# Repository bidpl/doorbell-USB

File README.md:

# Wake On Doorbell (WoD) USB Dongle

A USB stick that sends a spacebar press when the doorbell is pressed. Used to wake a door surveillence monitor when someone rings the doorbell.

Takes a AC signal through the barrel jack (doorbell wires). The onboard microcontroller acts as a USB keyboard while monitoring the signal for a drop in the average voltage (doorbell pressed). When it detects the decrease in voltage, it sends a spacebar keypress to wake the computer.

Assembled WoD USB Dongle:

WoD USB Dongle installed on a PC

## The stick itself

v1.0
Yay it works!
No errors found during testing and use.

## Case

A press fit case for the PCB. It has some screw holes, but the press fit is enough to hold it in. The tab for the USB connector is sized to increase the thickness of the connector to ~2.2mm.

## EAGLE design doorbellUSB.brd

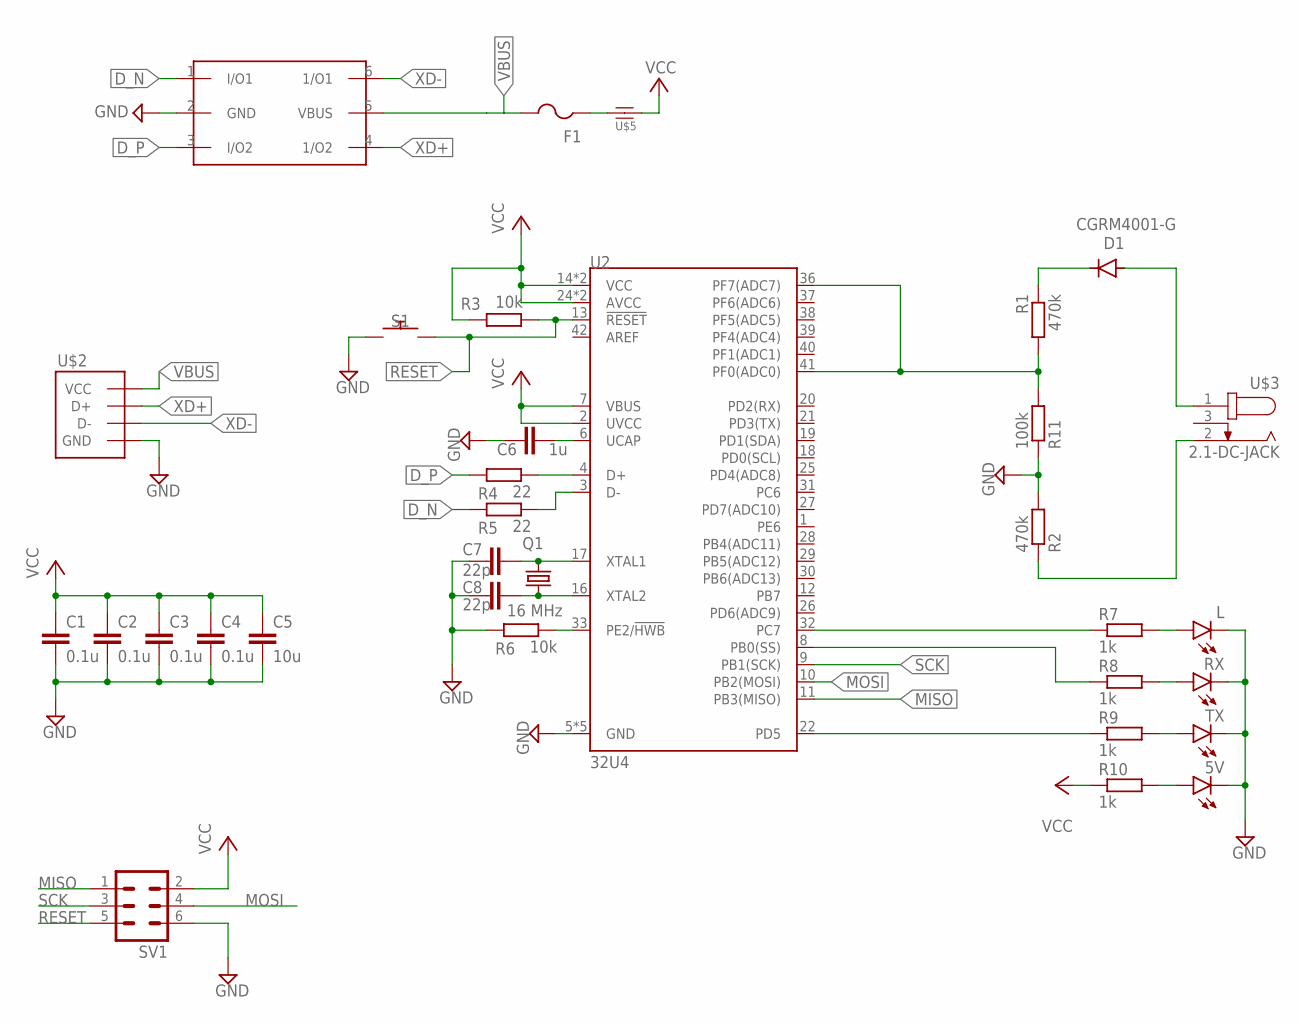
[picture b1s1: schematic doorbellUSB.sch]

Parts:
5V: LEDCHIP-LED0805; CHIP-LED0805
C1, C2, C3, C4: 0.1u; C0805
C5: 10u; C0805
C6: 1u; C0805
C7, C8: 22p; C0805
D1: CGRM4001-G; SOD-123_MINI-SMA
F1: PTCFUSE-1812; 1812
L: LEDCHIP-LED0805; CHIP-LED0805
Q1: 16 MHz; 5.0X3.2_2
R1, R2: 470k; R0805
R3, R6: 10k; R0805
R4, R5: 22; R0805
R7, R8, R9, R10: 1k; R0805
R11: 100k; R0805
RX: LEDCHIP-LED0805; CHIP-LED0805
S1: 3X4MM-PUHSBUTTON; 3X4MM-PUSHBUTTON
SV1: MA03-2
TX: LEDCHIP-LED0805; CHIP-LED0805
U2: 32U4; TQFP44
U$1: USBLC-2; SOT23-6L
U$2: PCB-USB-A; USB-A-ONBOARD
U$3: 2.1-DC-JACK; 2.1X5.5MM_JACK
U$5: FERRITE-BEAD; R0805

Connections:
DATA_N: R5.2, U2.3 (D-)
DATA_P: R4.2, U2.4 (D+)
D_N: R5.1, U$1.1 (I/O1)
D_P: R4.1, U$1.3 (I/O2)
GND: 5V.C, C1.2, C2.2, C3.2, C4.2, C5.2, C6.1, C7.2, C8.2, L.C, R2.2, R6.1, R11.1, RX.C, S1.P$1, SV1.6, TX.C, U2.5 (GND), U2.15 (GND), U2.23 (GND), U2.35 (GND), U2.43 (GND), U$1.2 (GND), U$2.GND
MISO: SV1.1, U2.11 (PB3(MISO))
MOSI: SV1.4, U2.10 (PB2(MOSI))
unnamed: R2.1, U$3.2
unnamed: D1.A, U$3.1
unnamed: D1.C, R1.1
unnamed: R1.2, R11.2, U2.36 (PF7(ADC7)), U2.41 (PF0(ADC0))
unnamed: R8.1, U2.8 (PB0(SS))
unnamed: C6.2, U2.6 (UCAP)
unnamed: R9.1, U2.22 (PD5)
unnamed: R7.1, U2.32 (PC7)
unnamed: L.A, R7.2
unnamed: R9.2, TX.A
unnamed: R6.2, U2.33 (PE2/!HWB)
unnamed: F1.1, U$5.2
unnamed: R8.2, RX.A
unnamed: 5V.A, R10.2
RESET: R3.2, S1.P$2, SV1.5, U2.13 (!RESET)
SCK: SV1.3, U2.9 (PB1(SCK))
VBUS: F1.2, U$1.5 (VBUS), U$2.VCC
VCC: C1.1, C2.1, C3.1, C4.1, C5.1, R3.1, R10.1, SV1.2, U2.2 (UVCC), U2.7 (VBUS), U2.14 (VCC), U2.24 (AVCC), U2.34 (VCC), U2.44 (AVCC), U$5.1
XD+: U$1.4 (1/O2), U$2.D+
XD-: U$1.6 (1/O1), U$2.D-
XTAL_1: C8.1, Q1.1, U2.16 (XTAL2)
XTAL_2: C7.1, Q1.2, U2.17 (XTAL1)

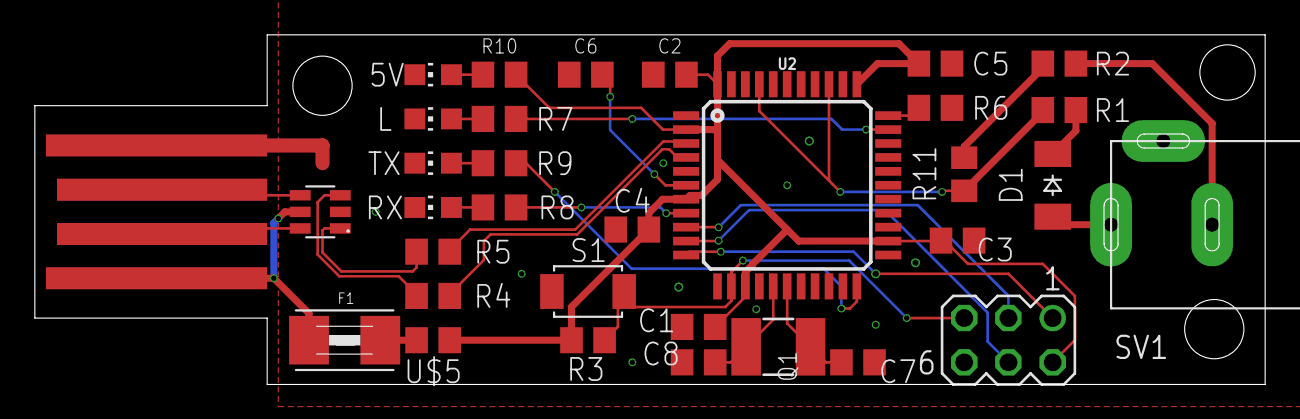
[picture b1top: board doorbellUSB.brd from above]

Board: 2 copper layers, 70.6 x 20.1 mm, 33 parts (0 on the bottom side), 29 nets.

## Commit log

2022-01-24 Turned project into git repo. Added images and README.md
2022-01-24 Cropped assembledUSB.jpg, edited README.md (reordered images and captions.

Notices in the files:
parts and their libraries:
crystal-geyer_V1_0: Copyright: Geyer-Electronic
